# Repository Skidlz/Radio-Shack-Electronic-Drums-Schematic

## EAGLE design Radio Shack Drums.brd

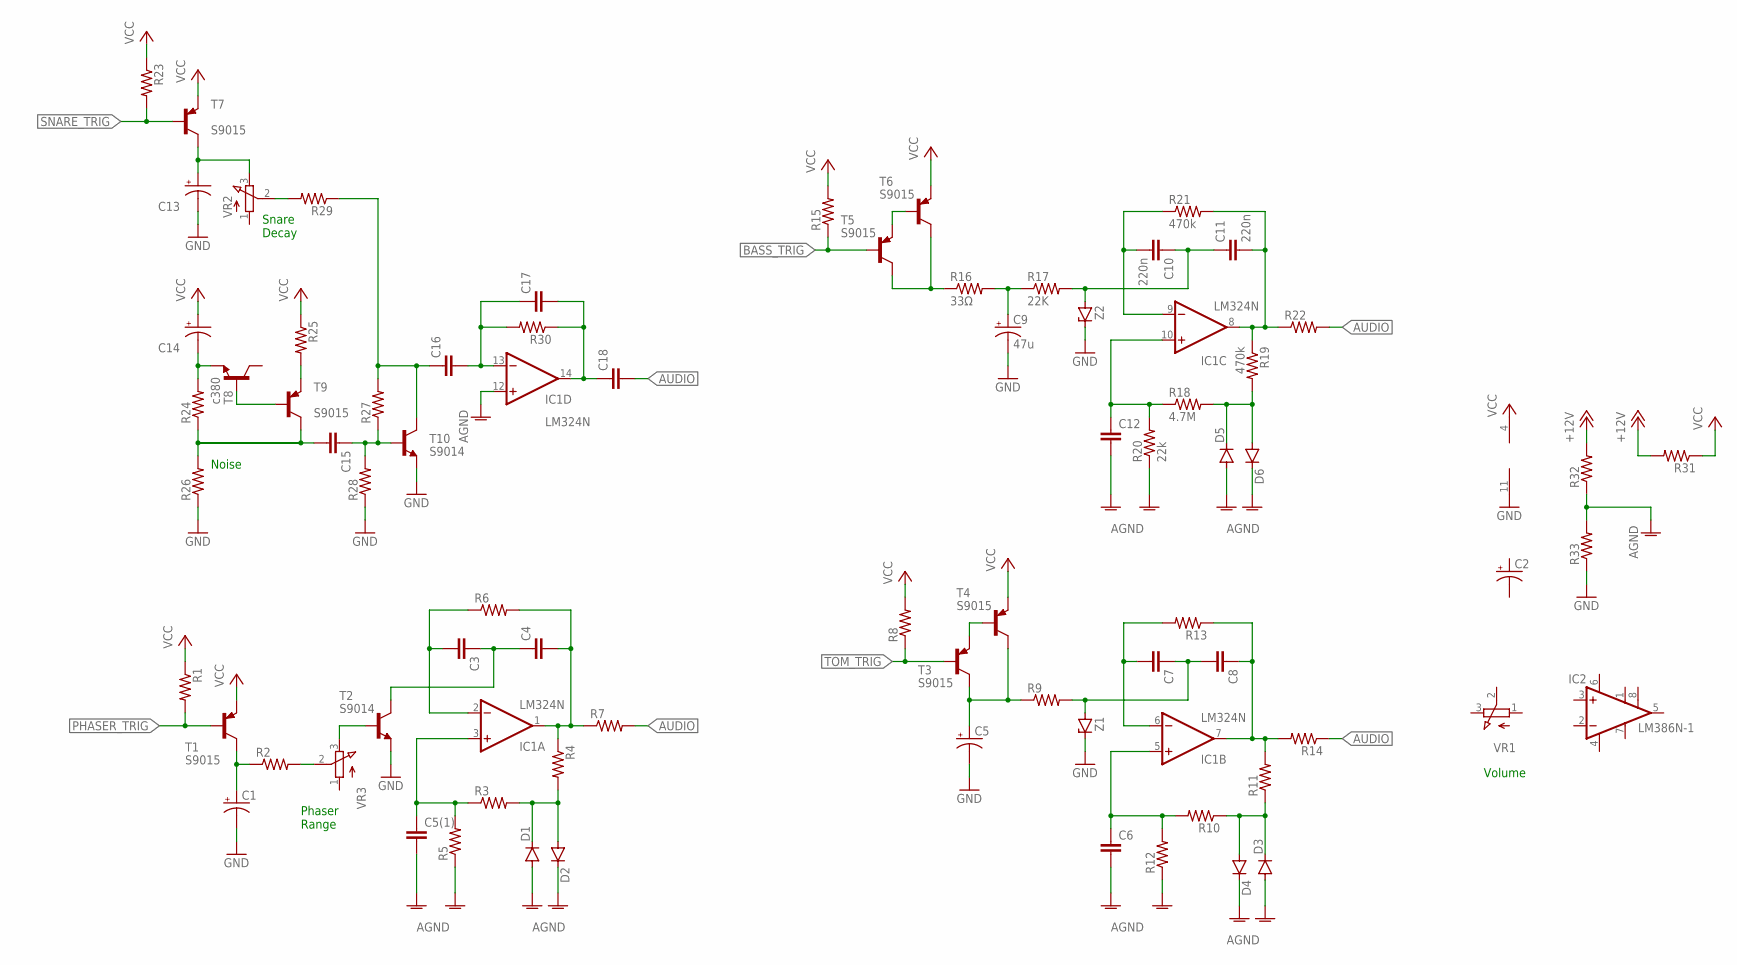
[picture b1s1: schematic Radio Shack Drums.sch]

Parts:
C1, C2, C5, C13, C14: CPOL-USTT2D4L; TT2D4L
C3, C4, C5(1), C6, C7, C8, C12, C15, C16: C-EU075-032X103; C075-032X103
C9: 47u; TT2D4L
C10, C11: 220n; C075-032X103
C17, C18: C-EU050-024X044; C050-024X044
D1, D2, D3, D4, D5, D6: DIODE-D-5; D-5
IC1: LM324N; DIL14
IC2: LM386N-1; DIL08
R1, R2, R3, R4, R5, R6, R7, R8, R9, R10, R11, R12, R13, R14, R15, R22, R23, R24, R25, R26, R27, R28, R29, R30, R31, R32, R33: R-US_0207/10; 0207/10
R16: 33Ω; 0207/10
R17: 22K; 0207/10
R18: 4.7M; 0207/10
R19, R21: 470k; 0207/10
R20: 22k; 0207/10
T1, T3, T4, T5, T6, T7, T9: S9015; TO92
T2, T10: S9014; TO92
T8: c380; TO92-ECB
VR1, VR2, VR3: 3RP/1610N
Z1, Z2: ZENER-DIODEDO34-7; DO34Z7

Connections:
+12V: R31.2, R32.2
AGND: C5(1).2, C6.2, C12.2, D1.A, D2.C, D3.A, D4.C, D5.A, D6.C, IC1.12 (+IN), R5.1, R12.1, R20.1, R32.1, R33.2
AUDIO: C18.2, R7.2, R14.1, R22.2
BASS_TRIG: R15.1, T5.2 (B)
GND: C1.-, C5.-, C9.-, C13.-, IC1.11 (V-), IC2.4 (GND), R26.1, R28.1, R33.1, T2.1 (E), T10.1 (E), Z1.C, Z2.C
unnamed: T2.2 (B), VR3.3 (E)
unnamed: R2.2, VR3.2 (S)
unnamed: C1.+, R2.1, T1.3 (C)
unnamed: C3.1, C4.1, T2.3 (C)
unnamed: C3.2, IC1.2 (-IN), R6.1
unnamed: C4.2, IC1.1 (OUT), R4.1, R6.2, R7.1
unnamed: D1.C, D2.A, R3.2, R4.2
unnamed: C6.1, IC1.5 (+IN), R10.2, R12.2
unnamed: C5(1).1, IC1.3 (+IN), R3.1, R5.2
unnamed: D3.C, D4.A, R10.1, R11.1
unnamed: C7.1, C8.2, R9.2, Z1.A
unnamed: C7.2, IC1.6 (-IN), R13.2
unnamed: C8.1, IC1.7 (OUT), R11.2, R13.1, R14.2
unnamed: T5.1 (E), T6.2 (B)
unnamed: R16.1, T5.3 (C), T6.3 (C)
unnamed: T3.1 (E), T4.2 (B)
unnamed: C5.+, R9.1, T3.3 (C), T4.3 (C)
unnamed: C15.2, R24.1, R26.2, T9.3 (C)
unnamed: C9.+, R16.2, R17.1
unnamed: C10.1, C11.1, R17.2, Z2.A
unnamed: C10.2, IC1.9 (-IN), R21.1
unnamed: C11.2, IC1.8 (OUT), R19.1, R21.2, R22.1
unnamed: C12.1, IC1.10 (+IN), R18.1, R20.2
unnamed: D5.C, D6.A, R18.2, R19.2
unnamed: C13.+, T7.3 (C), VR2.3 (E)
unnamed: R29.2, VR2.2 (S)
unnamed: C17.2, C18.1, IC1.14 (OUT), R30.1
unnamed: C14.-, R24.2, T8.E
unnamed: R25.2, T9.1 (E)
unnamed: C15.1, R27.1, R28.2, T10.2 (B)
unnamed: C16.1, R27.2, R29.1, T10.3 (C)
unnamed: T8.B, T9.2 (B)
unnamed: C16.2, C17.1, IC1.13 (-IN), R30.2
PHASER_TRIG: R1.2, T1.2 (B)
SNARE_TRIG: R23.2, T7.2 (B)
TOM_TRIG: R8.1, T3.2 (B)
VCC: C14.+, IC1.4 (V+), R1.1, R8.2, R15.2, R23.1, R25.1, R31.1, T1.1 (E), T4.1 (E), T6.1 (E), T7.1 (E)
VS: IC2.6 (VS)

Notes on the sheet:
Phaser Range
Noise
Snare Decay
Volume

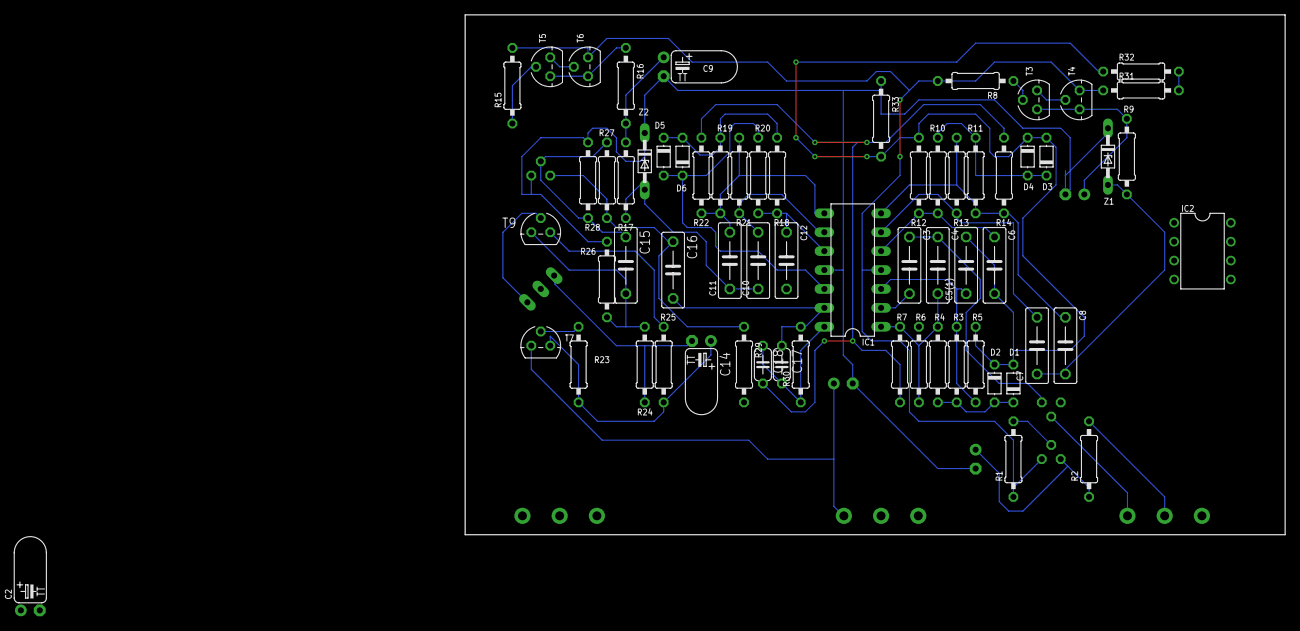
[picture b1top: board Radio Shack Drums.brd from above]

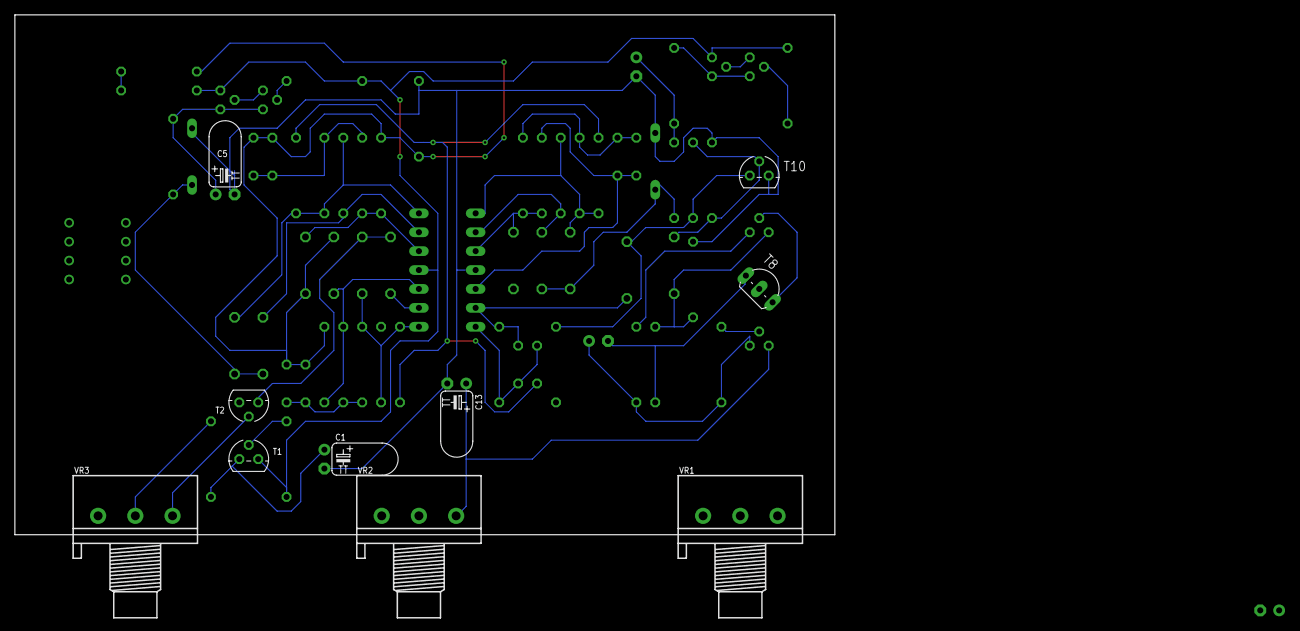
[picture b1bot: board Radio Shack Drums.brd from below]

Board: 2 copper layers, 110.2 x 69.8 mm, 75 parts (10 on the bottom side), 42 nets.

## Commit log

2020-03-15 Init
